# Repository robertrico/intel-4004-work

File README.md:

# intel-4004-work

Work toward running a real Intel 4004 safely, and eventually building a standalone 4004 calculator with no FPGA in it.

The chips are on loan: two 1970s boards, an HP MCS-4 Exerciser (COS-2) and a Pro-Log PWM 100674XA, each carrying a white ceramic C4004 with its 4001/4002/4008/4009/1702A companions. They are scarce and effectively irreplaceable, so chip safety outranks convenience everywhere in this repo. Nothing with a chip in it gets power until the empty-socket bench plan passes.

## Plan

1. **Bench harness.** A 3.3 V host (ECP5 FPGA first, Pico 2 as the alternative) drives and reads a 4004 through discrete level shifting. Rails VSS +15 V, VDD ground. Drive side: CD4504B for the two clocks and for the gates of TP0606 P-FETs that make a tri-state push-pull on the four bus lines, BS170 open drain for TEST and RESET. Receive side: LM2901 comparators from +15 V against an 11.5 V reference, open collector pulled up to 3.3 V. The FPGA is bench gear only.
2. **Reverse-engineer the loaned boards**, statically, with a meter and power off, before any of them sees power.
3. **Standalone calculator.** Intel's +5 / −10 V rails, real MCS-40 parts for clock, memory and I/O. The TTL clock timing section carries over from the harness; its CD4504B level stage does not.

## Layout

| Path | What |
|---|---|
| `docs/tutorial.md` | Step-by-step walkthrough from what arrives to a program blinking an LED. Start here. |
| `docs/stage0-bench-plan.md` | Empty-socket test plan with pass criteria: rails, level shifters, signal-generator learning sequence. |
| `docs/bench-measurements.md` | Running list of things the simulation or the design review said to measure on the bench, with results as they come in. |
| `docs/clock-generator.md` | Two-phase 4004 clock in TTL from shelf parts: 24.545 MHz can, 74S163, 74LS163A, 74LS74, 74LS00, CD4504B. Pin tables and scope checklist. |
| `docs/pattern-generator-555-cd4029.md` | NE555 + CD4029B at 15 V, a four-line 0 / 15 V counting pattern that stands in for the 4004 on the bench. |
| `docs/pmos-level-shifting-notes.md` | The analysis: 4004 datasheet limits, the owner's circuit checked against them, every part's datasheet numbers. Section 1 is earlier 8008 reasoning that led here. |
| `docs/spice-lessons.md` | Learning the KiCad simulator (ngspice) lesson by lesson, with the power sheet simulated and the clamp-zener tolerance experiment. |
| `docs/baker-4004-sbc.md` | Scott Baker's 4004/4040 SBC read as prior art for the calculator: Intel rails, 4201 clock, 4289 and 4265 as the level shifters. |
| `docs/hp-board-reverse-engineering.md` | Five-step static plan for the HP board. |
| `docs/reviews/` | Design review rounds of the host interface schematic. |
| `hardware/host-interface/` | KiCad 10 project of the bench harness: power, clock, host buffers, line drivers, receivers, 4004 socket. `4004-host-interface.pdf` is the export. ERC clean. |
| `hardware/spice-tests/` | KiCad scratch project for the simulator lessons; sub-sheet `power` is the simulated power sheet. |
| `bom/` | Parts list with each part's role and the datasheet number behind it, plus the matching Mouser cart upload. |
| `datasheets/` | BS170, LM2901, TP0606, LM319, Traco TMR 1, CD4029B, and from [bitsavers](http://www.bitsavers.org/components/intel/MCS4/) the MCS-40 User's Manual (Nov 1974) and Advance Specifications (Sep 1974). |
| `reference/` | The [RetroShield k4004s](https://github.com/8bitforce/retroshield-hw) PCB imported from gEDA. Prior art only, not this design. |

## Conventions

- Intel datasheets and measurement are the authority. Prior-art boards and the owner's circuit are evidence.
- Guaranteed margins over typical values.
- KiCad files are edited in KiCad or through tooling that preserves them, never by hand.
- Through-hole only.

## Prior art

Studied, not copied:

- 8bitforce RetroShield: [hardware](https://github.com/8bitforce/retroshield-hw), [Teensy firmware](https://github.com/8bitforce/retroshield-teensy), [8bitforce.com](https://8bitforce.com)
- Scott Baker's 4004/4040 single board computer: [repository](https://github.com/sbelectronics/4004), [write-up](https://www.smbaker.com/?p=3953)
- Intel MCS-4 and MCS-40 documentation on [bitsavers](http://www.bitsavers.org/components/intel/MCS4/), including the 4004 datasheet, the MCS-4 User's Manual (1973), the MCS-40 User's Manual (1974) and the MCS-40 Advance Specifications (1974)
- Traco [TMR 1 series](https://www.tracopower.com/tmr1-datasheet) DC/DC converter datasheet

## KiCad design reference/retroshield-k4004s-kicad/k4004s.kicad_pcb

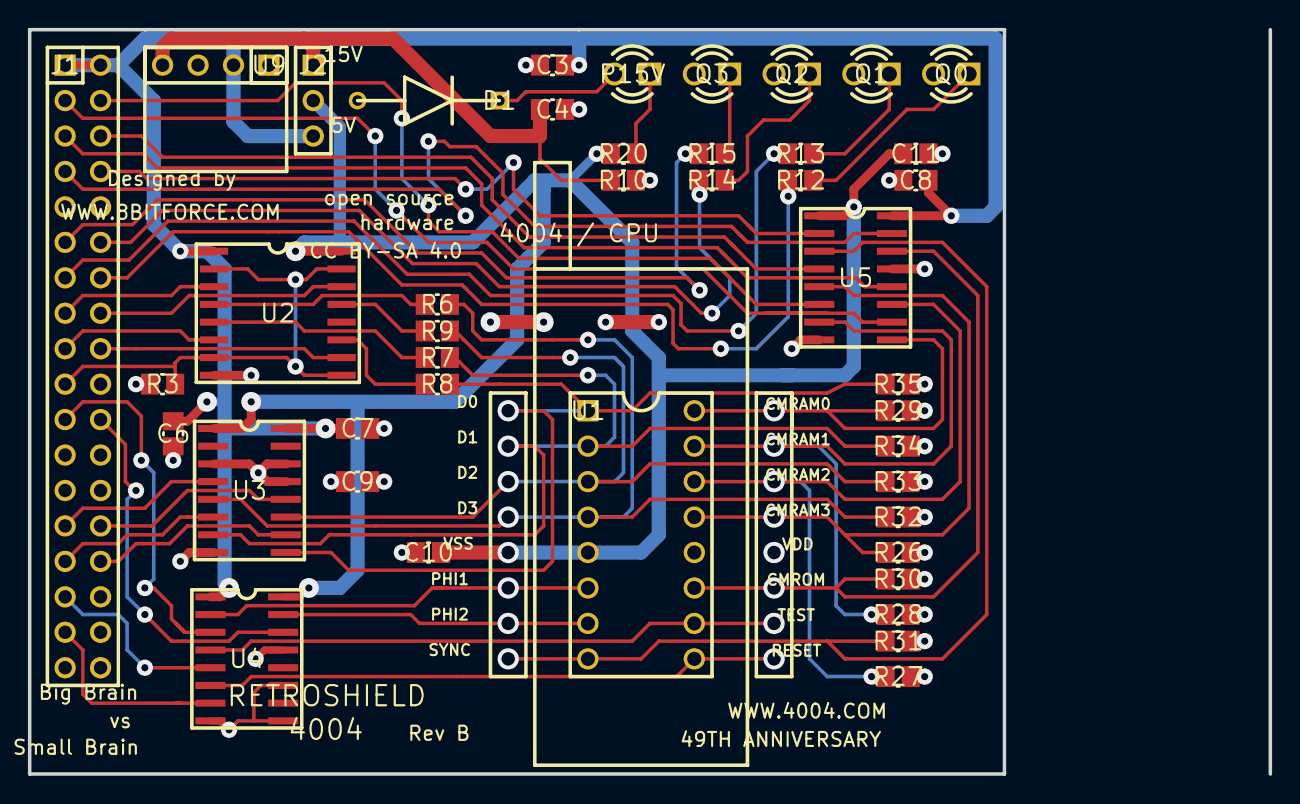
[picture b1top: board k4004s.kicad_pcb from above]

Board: 2 copper layers, 69.8 x 53.3 mm, 43 parts (0 on the bottom side), 51 nets.

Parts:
C3, C4: 4.7uF
C6, C7, C8, C9, C10, C11: 100NF
D1: 5V6
J1, J2: unknown
P15V: unknown
Q0, Q1, Q2, Q3: unknown
R3, R10, R26, R27, R28, R29, R30, R31, R32, R33, R34, R35: 10K
R6, R7, R8, R9, R12, R13, R14, R15: 680
R20: 3.1K
U1, U2, U3, U4, U5, U9: unknown

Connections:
+5V: C3.2, C6.2, C7.2, C8.2, J1.1, J1.36, J2.3, U2.1, U3.16, U4.1, U5.16, U9.2
ARDUINO_D0: J1.28, U2.10
ARDUINO_D1: J1.9, U2.6
ARDUINO_D2: J1.29, U2.14
ARDUINO_D3: J1.8, U2.3
CMRAM0_5V: J1.2, U5.10
CMRAM0_4004: R29.1, U1.16, U5.9
CMRAM1_5V: J1.35, U5.6
CMRAM1_4004: R28.1, U1.15, U5.7
CMRAM2_5V: J1.3, U5.12
CMRAM2_4004: R27.1, U1.14, U5.11
CMRAM3_5V: J1.34, U5.4
CMRAM3_4004: R26.1, U1.13, U5.5
CMROM_5V: J1.4, U5.15
CMROM_4004: R30.1, U1.11, U5.14
CPU_D0_5V: J1.22, U3.10
CPU_D1_5V: J1.15, U3.6
CPU_D2_5V: J1.23, U3.12
CPU_D3_5V: J1.14, U3.4
D0_15V: R8.2, R35.1, U1.1, U3.9
D1_15V: R7.2, R34.1, U1.2, U3.7
D2_15V: R9.2, R33.1, U1.3, U3.11
D3_15V: R6.2, R32.1, U1.4, U3.5
DRIVE_DBUS: J1.10, R3.2, U2.2, U2.7, U2.9, U2.15
GND: C3.1, C4.1, C6.1, C7.1, C8.1, C9.1, C10.1, C11.1, D1.2, J1.18, J1.19, Q0.2, Q1.2, Q2.2, Q3.2, R3.1, R10.1, R26.2, R27.2, R28.2, R29.2, R30.2, R31.2, R32.2, R33.2, R34.2, R35.2, U1.12, U2.8, U3.3, U3.8, U3.13, U3.14, U4.8, U4.9, U4.11, U4.13, U5.8, U5.13, U9.1, U9.3
P15V: C9.2, C10.2, C11.2, J2.2, R20.2, U1.5, U2.16, U3.1, U4.16, U5.1
PHI1: J1.11, U4.3
PHI1_15V: U1.6, U4.2
PHI2: J1.26, U4.14
PHI2_15V: U1.7, U4.15
RAM_Q0_5V: J1.30, R12.1
RAM_Q1_5V: J1.7, R13.1
RAM_Q2_5V: J1.31, R14.1
RAM_Q3_5V: J1.6, R15.1
RESET: J1.17, U4.7
RESET_15V: U1.9, U4.6
SYNC_5V: J1.33, U5.2
SYNC_4004: R31.1, U1.8, U5.3
TEST: J1.16, U4.5
TEST_15V: U1.10, U4.4
unnamed_net1: P15V.1, R20.1
unnamed_net2: D1.1, P15V.2
unnamed_net3: R7.1, U2.5
unnamed_net4: R6.1, U2.4
unnamed_net5: R8.1, U2.11
unnamed_net6: R9.1, U2.13
unnamed_net7: Q0.1, R12.2
unnamed_net8: Q1.1, R13.2
unnamed_net9: Q2.1, R14.2
unnamed_net10: Q3.1, R15.2
unnamed_net11: C4.2, J2.1, R10.2, U9.4

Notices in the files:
reference/retroshield-k4004s-kicad/k4004s.kicad_pcb:
CC BY-SA 4.0
